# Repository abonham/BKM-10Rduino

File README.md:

# BKM-10Rduino

This project has moved to [BKM-10Replacements](https://github.com/abonham/BKM-10Replacements) to reflect the multiple different board types it now supports.

The Raspberry Pico based BKM-10Rp2040 is the recommended and most up-to-date version now.

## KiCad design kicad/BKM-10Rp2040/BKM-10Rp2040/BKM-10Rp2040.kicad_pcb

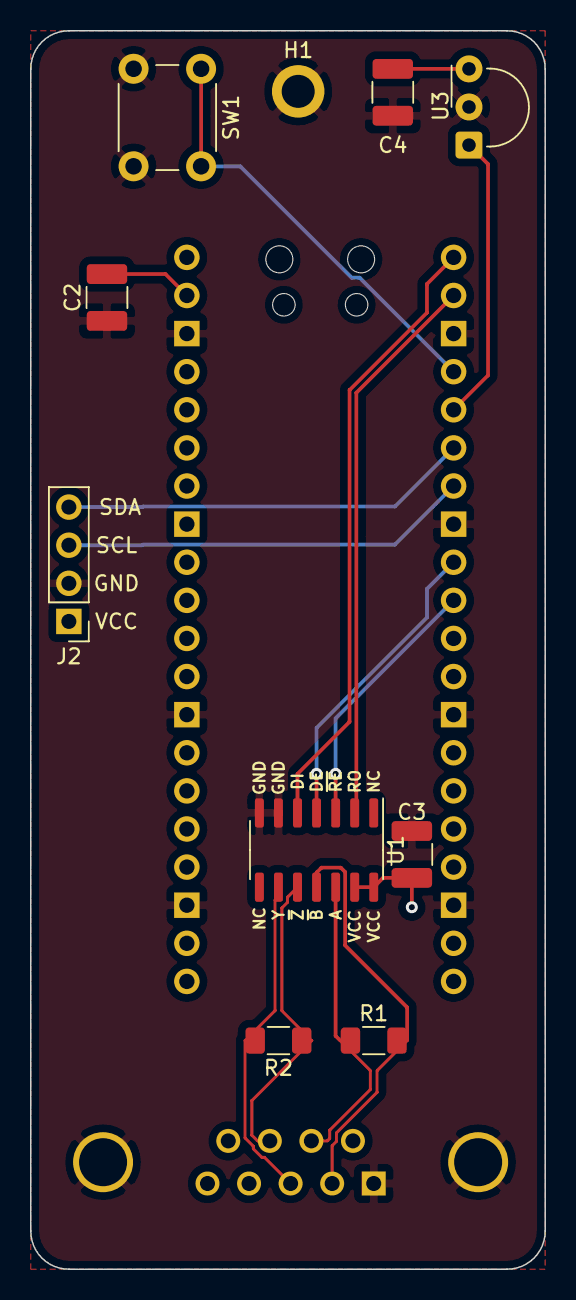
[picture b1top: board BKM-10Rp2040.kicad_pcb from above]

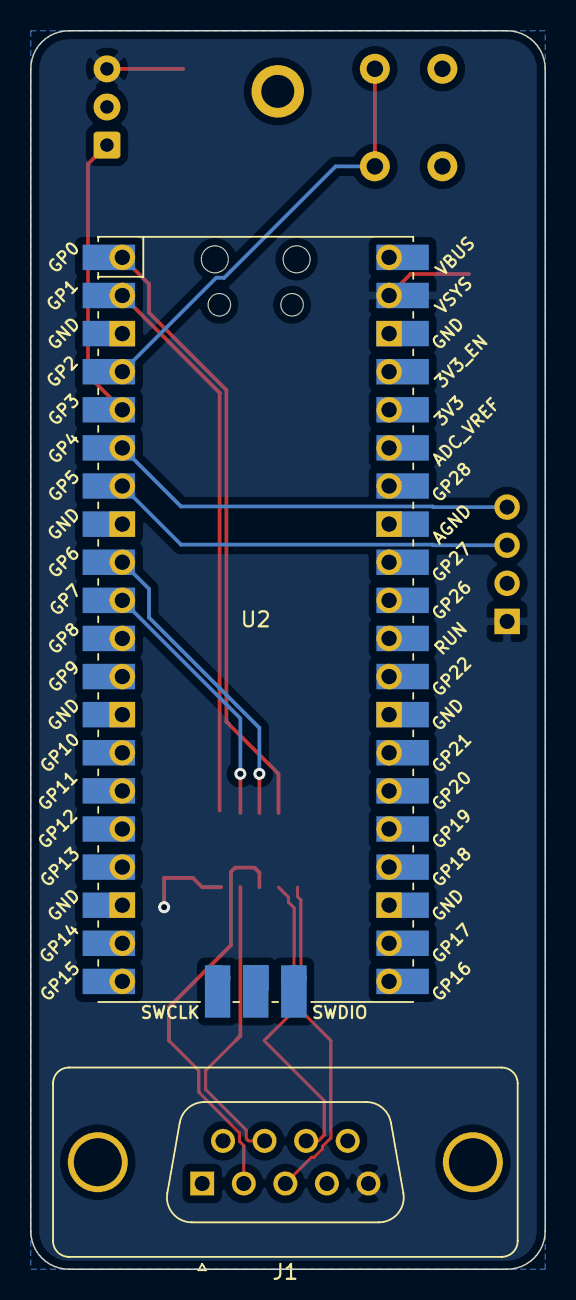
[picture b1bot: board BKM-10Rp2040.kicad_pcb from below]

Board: 2 copper layers, 34.3 x 82.5 mm, 12 parts (2 on the bottom side), 14 nets.

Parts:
C2, C4: 0.1uF; C_1210_3225Metric_Pad1.33x2.70mm_HandSolder
C3: 1uF; C_1210_3225Metric_Pad1.33x2.70mm_HandSolder
H1: MountingHole_Pad; MountingHole_2.2mm_M2_ISO7380_Pad
J1: DB9_Female_MountingHoles; DSUB-9_Female_Vertical_P2.77x2.84mm_MountingHoles
J2: Conn_01x04; PinHeader_1x04_P2.54mm_Vertical
R1, R2: 60R; R_1206_3216Metric_Pad1.30x1.75mm_HandSolder
SW1: SW_DPST_x2; SW_PUSH_6mm
U1: ADM3063EARZ-ND; SOIC-14_3.9x8.7mm_P1.27mm
U2: Pico; RPi_Pico_SMD_TH
U3: TSOP335xx; Vishay_MINIMOLD-3Pin

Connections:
+5V: C2.2, C3.1, C4.1, J1.5, J2.1, U1.13, U1.14, U2.39, U3.3
DE: U1.4, U2.9
GND: C2.1, C3.2, C4.2, H1.1, J1.0, J1.1, J2.2, SW1.2, U1.6, U1.7, U2.3, U2.8, U2.13, U2.18, U2.23, U2.28, U2.38, U3.2
IR: U2.5, U3.1
LEARN: SW1.1, U2.4
RX: U1.2, U2.2
RXD+: J1.3, R2.2, U1.9
RXD-: J1.8, R2.1, U1.10
SCL: J2.3, U2.7
SDA: J2.4, U2.6
TX: U1.5, U2.1
TXD+: J1.7, R1.1, U1.12
TXD-: J1.2, R1.2, U1.11
~RE~: U1.3, U2.10

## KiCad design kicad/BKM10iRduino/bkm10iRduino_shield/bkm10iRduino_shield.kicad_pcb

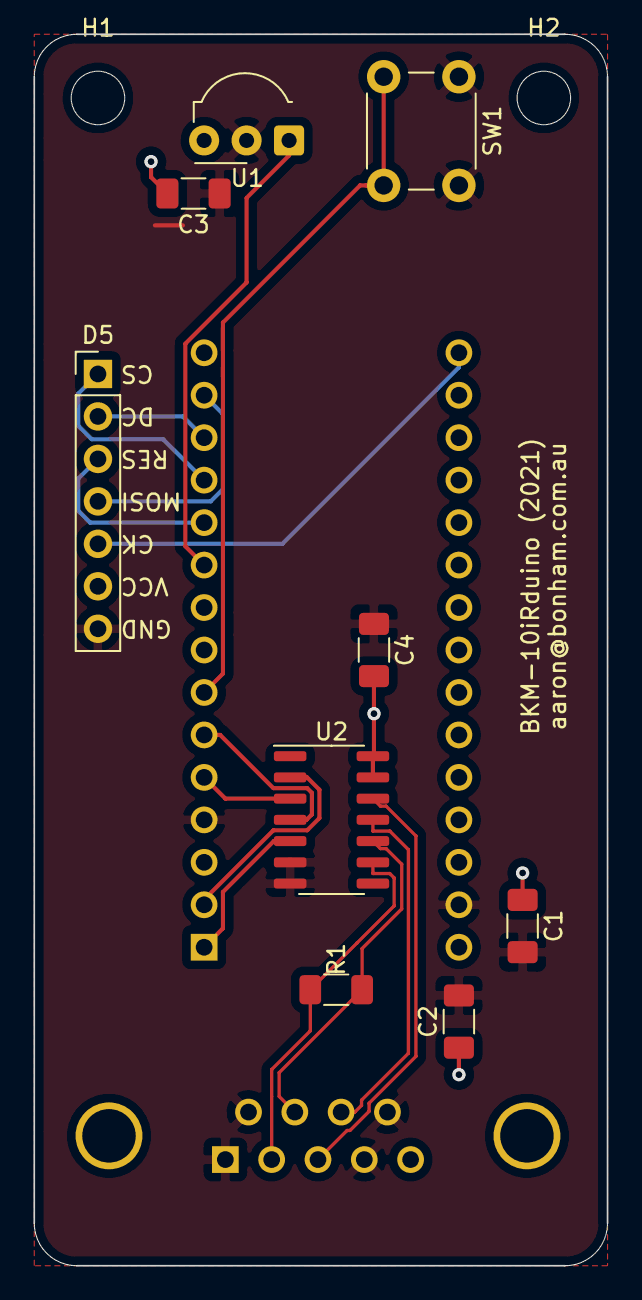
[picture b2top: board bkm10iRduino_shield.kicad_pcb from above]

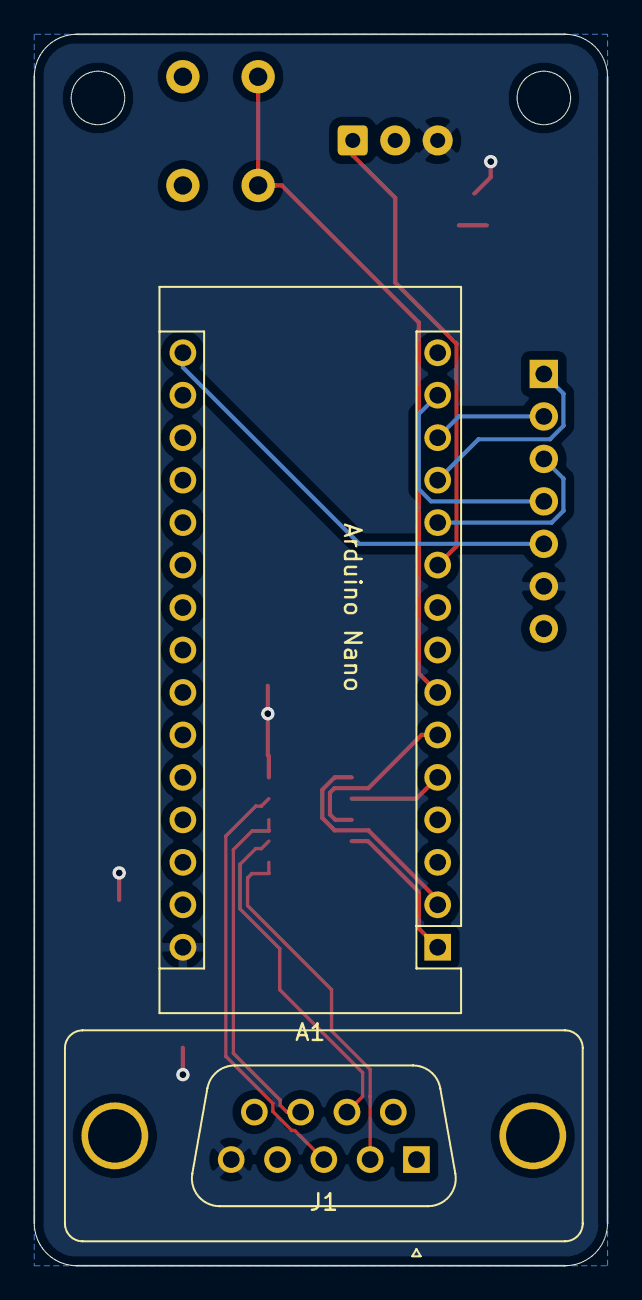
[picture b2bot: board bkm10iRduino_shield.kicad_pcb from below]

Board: 2 copper layers, 34.3 x 73.7 mm, 13 parts (2 on the bottom side), 17 nets.

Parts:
A1: Arduino_Nano_Every; Arduino_Nano
C1, C2, C3, C4: C_Small; C_1206_3216Metric_Pad1.33x1.80mm_HandSolder
D5: SH1106; PinHeader_1x07_P2.54mm_Vertical
H1, H2: MountingHole; MountingHole_3.2mm_M3
J1: DB9_Male; DSUB-9_Male_Vertical_P2.77x2.84mm_MountingHoles
R1: R; R_1206_3216Metric_Pad1.30x1.75mm_HandSolder
SW1: SW_SPST; SW_PUSH_6mm_H5mm
U1: TSOP343xx; Vishay_MOLD-3Pin
U2: ADM3063EARZ-ND; SOIC-14_3.9x8.7mm_P1.27mm

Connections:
AB+: J1.8, U2.11
AB-: J1.3, U2.12
CS: A1.12, D5.1
DC: A1.13, D5.2
GND: A1.4, A1.29, C1.2, C2.2, C3.1, C4.1, D5.7, J1.1, J1.4, J1.6, J1.9, SW1.1, U1.2, U2.6, U2.7
IR_OUT: A1.10, U1.1
LEARN_BUTTON_IN: A1.7, SW1.2
MOSI: A1.14, D5.4
RES: A1.11, D5.3
RS485_RX: A1.2, U2.2
RS485_RX_ENABLE: A1.5, U2.3
RS485_TX: A1.1, U2.5
RS485_TX_ENABLE: A1.6, U2.4
SCK: A1.16, D5.5
VCC: A1.30, C1.1, C2.1, C3.2, C4.2, D5.6, J1.5, U1.3, U2.13, U2.14
YZ+: J1.2, R1.1, U2.9
YZ-: J1.7, R1.2, U2.10

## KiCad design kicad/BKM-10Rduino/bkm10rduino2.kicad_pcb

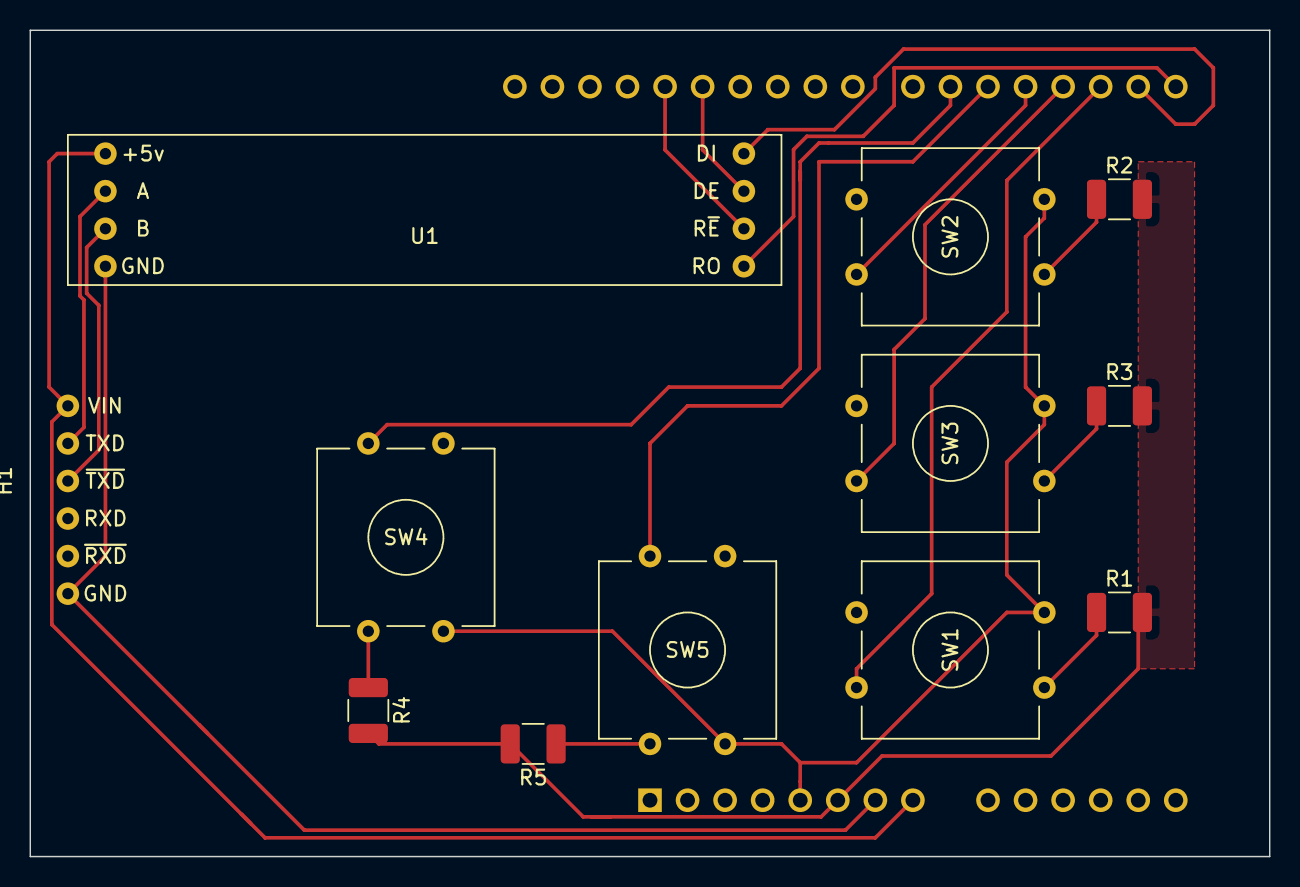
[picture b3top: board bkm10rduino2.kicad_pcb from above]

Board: 2 copper layers, 83.8 x 55.9 mm, 13 parts (1 on the bottom side), 20 nets.

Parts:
A1: Arduino_UNO_R3
H1: 6_PIN_HEADER
R1, R2, R3, R4, R5: R; R_1210_3225Metric_Pad1.30x2.65mm_HandSolder
SW1, SW2, SW3, SW4, SW5: SW_MEC_5E_copy; SW_Tactile_SPDP_12.3_5mm
U1: TLL_TO_RS485; TLL_RS485

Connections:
/5v: A1.5, SW1.3, SW2.3, SW3.3, SW4.3, SW5.3
/DE: A1.27, U1.6
/RE: A1.28, U1.7
/RX: A1.15, U1.8
/TX: A1.16, U1.5
/b0: A1.17, SW1.2
/b1: A1.18, SW3.2
/b2: A1.19, SW2.2
/b3: A1.20, SW5.2
/b4: A1.21, SW4.2
/g1: A1.6, R1.2, R2.2, R3.2, R4.2, R5.2
/g2: A1.7, H1.6, U1.4
unnamed: A1.8, H1.1, U1.1
unnamed: H1.2, U1.2
unnamed: H1.3, U1.3
unnamed: R1.1, SW1.1
unnamed: R2.1, SW2.1
unnamed: R3.1, SW3.1
unnamed: R4.1, SW4.1
unnamed: R5.1, SW5.1

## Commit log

2021-10-21 add readme
2021-10-22 add ir version
2021-10-22 tyop
2021-10-22 formatting
2021-10-23 update kicad layout
2021-10-24 add full board kicad project
2021-10-24 fix beginneer mistakes on all controls
2021-10-27 add schematic and design for IR board
2021-10-30 combine IR and buttons, WIP learning mode
2021-10-30 add debug define
2021-10-31 minor clean up
2021-11-07 wip learning mode
2021-11-07 learning mode done for now
2021-11-07 seems to be working
2021-11-07 tidy up code
2021-11-07 add all remaining commands
2021-11-07 improve feedback on display
2021-11-07 update pcb
2021-11-08 updated pcb design
2021-11-09 update pins
2021-11-10 pcb redesign
2021-11-14 more updates to board
2021-11-29 many fixes to pcb layout, use full duplex RS485
2021-11-29 move older version
2021-12-01 start RP2040 version
2021-12-02 add 2 layer PBC and also a RP2040 version
2021-12-03 revert full duplex changes
2021-12-15 get started on RP2040 version
2021-12-15 get started on status LEDs
2021-12-15 LED logic
2021-12-15 leds working
2021-12-15 tidy up
2021-12-17 safer logging
2021-12-20 add cocktail mode to oled :)
2021-12-20 update readme image
2021-12-21 fix rotary selection display
2021-12-22 add rotary buttons to setup
2021-12-24 new version of case
2021-12-24 remove old files
2022-01-13 tidying up and readying RP2040 version
2022-01-15 fix rp2040 design
2022-01-20 add new rp2040 code
2022-03-05 update platform.io config
2022-04-11 remove all code and update readme to point to new project
2022-04-11 add new link
